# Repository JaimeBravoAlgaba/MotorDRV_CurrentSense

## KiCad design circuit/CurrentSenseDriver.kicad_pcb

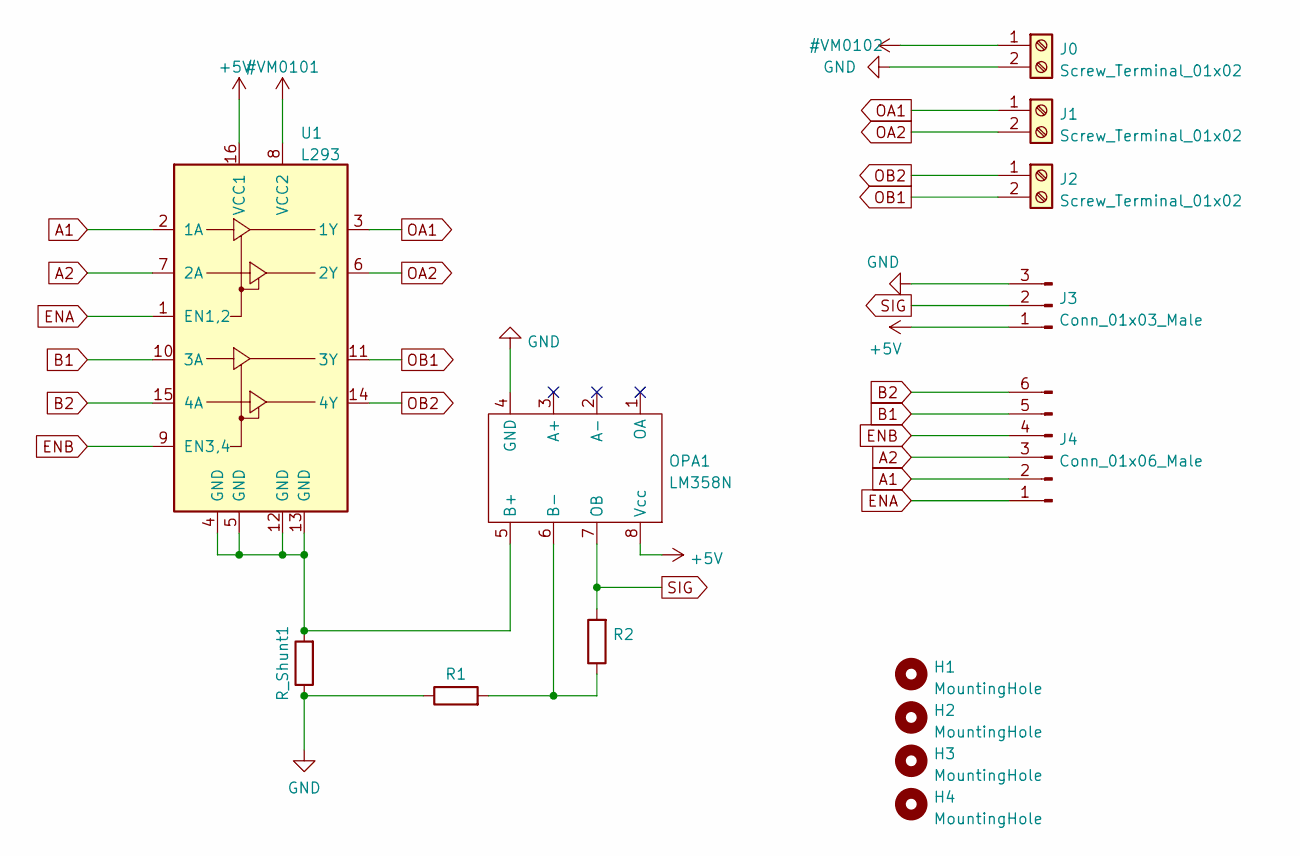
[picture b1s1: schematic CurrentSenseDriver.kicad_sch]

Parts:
H1, H2, H3, H4: MountingHole; MountingHole_3.2mm_M3
J0, J1, J2: Screw_Terminal_01x02; PinSocket_1x02_P2.54mm_Vertical
J3: Conn_01x03_Male; PinSocket_1x03_P2.54mm_Vertical
J4: Conn_01x06_Male; PinSocket_1x06_P2.54mm_Vertical
OPA1: LM358N; DIP-8_W7.62mm
R1, R2: R; R_Axial_DIN0207_L6.3mm_D2.5mm_P10.16mm_Horizontal
R_Shunt1: R; R_Axial_DIN0414_L11.9mm_D4.5mm_P15.24mm_Horizontal
U1: L293; DIP-16_W7.62mm

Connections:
+5V: J3.1, OPA1.8 (Vcc), U1.16 (VCC1)
A1: J4.2, U1.2 (1A)
A2: J4.3, U1.7 (2A)
B1: J4.5, U1.10 (3A)
B2: J4.6, U1.15 (4A)
ENA: J4.1, U1.1 (EN1,2)
ENB: J4.4, U1.9 (EN3,4)
GND: J0.2, J3.3, OPA1.4 (GND), R1.1, R_Shunt1.1; also elsewhere on the board
unnamed 8: OPA1.5 (B+), R_Shunt1.2, U1.4 (GND), U1.5 (GND), U1.12 (GND), U1.13 (GND); also elsewhere on the board
unnamed: OPA1.6 (B-), R1.2, R2.1
OA1: J1.1, U1.3 (1Y)
OA2: J1.2, U1.6 (2Y)
OB1: J2.2, U1.11 (3Y)
OB2: J2.1, U1.14 (4Y)
SIG: J3.2, OPA1.7 (OB), R2.2
VDC: J0.1, U1.8 (VCC2)

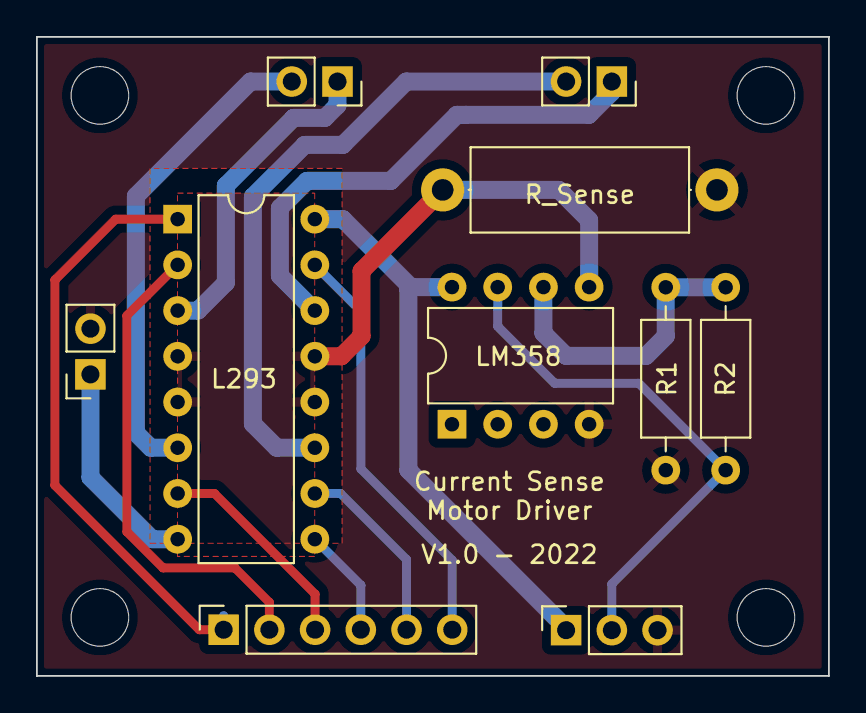
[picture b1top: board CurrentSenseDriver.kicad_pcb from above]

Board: 2 copper layers, 44.0 x 35.5 mm, 14 parts (0 on the bottom side), 16 nets.

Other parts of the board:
R_Sense: R; R_Axial_DIN0414_L11.9mm_D4.5mm_P15.24mm_Horizontal

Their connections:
GND: R_Sense.1; also elsewhere on the board
unnamed 8: R_Sense.2; also elsewhere on the board

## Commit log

2022-10-09 V1.0
